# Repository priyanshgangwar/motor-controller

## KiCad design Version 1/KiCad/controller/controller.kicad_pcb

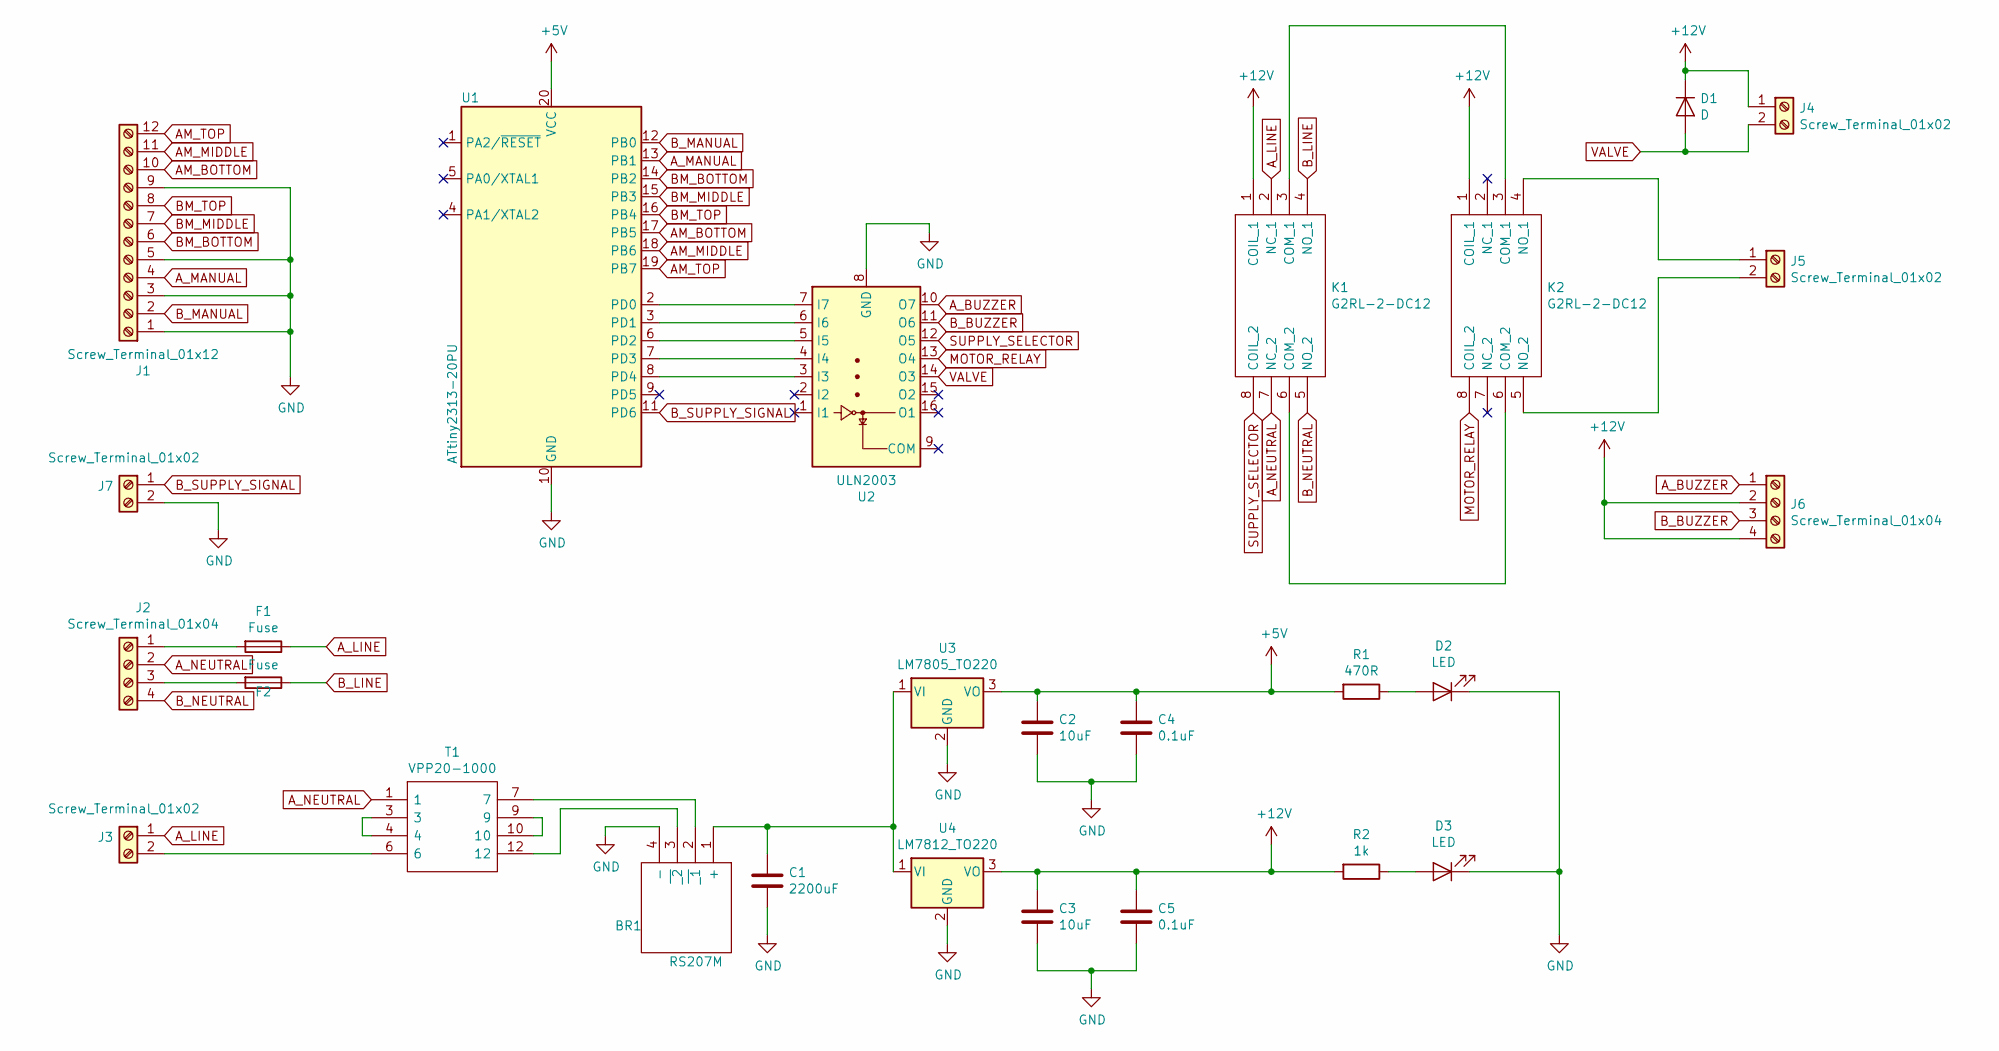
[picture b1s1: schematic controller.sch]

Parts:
BR1: RS207M; Mouser Part Number 583-RS207M
C1: 2200uF; CP_Radial_D16.0mm_P7.50mm
C2, C3: 10uF; CP_Radial_D5.0mm_P2.00mm
C4, C5: 0.1uF; CP_Radial_D5.0mm_P2.00mm
D1: D; D_DO-41_SOD81_P12.70mm_Horizontal
D2, D3: LED; LED_D5.0mm
F1, F2: Fuse; 646-SERIESHOLDER
J1: Screw_Terminal_01x12; TerminalBlock_Phoenix_MKDS-1,5-12_1x12_P5.00mm_Horizontal
J2, J6: Screw_Terminal_01x04; TerminalBlock_Phoenix_MKDS-1,5-4_1x04_P5.00mm_Horizontal
J3, J4, J5, J7: Screw_Terminal_01x02; TerminalBlock_Phoenix_MKDS-1,5-2_1x02_P5.00mm_Horizontal
K1, K2: G2RL-2-DC12; G2RL-24; Mouser Part Number 653-G2RL-2-DC12
R1: 470R; R_Axial_DIN0309_L9.0mm_D3.2mm_P12.70mm_Horizontal
R2: 1k; R_Axial_DIN0309_L9.0mm_D3.2mm_P12.70mm_Horizontal
T1: VPP20-1000; VPP201000; Mouser Part Number 553-VPP20-1000
U1: ATtiny2313-20PU; DIP-20_W7.62mm_Socket
U2: ULN2003; DIP-16_W7.62mm_Socket
U3: LM7805_TO220; TO-220-3_Vertical
U4: LM7812_TO220; TO-220-3_Vertical

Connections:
+5V: C2.1, C4.1, R1.2, U1.20 (VCC), U3.3 (VO)
+12V: C3.1, C5.1, D1.1 (K), J4.1, J6.2, J6.4, K1.1 (COIL_1), K2.1 (COIL_1), R2.2, U4.3 (VO)
AM_BOTTOM: J1.10, U1.17 (PB5)
AM_MIDDLE: J1.11, U1.18 (PB6)
AM_TOP: J1.12, U1.19 (PB7)
A_BUZZER: J6.1, U2.10 (O7)
A_LINE: F1.1, J3.1, K1.2 (NC_1)
A_MANUAL: J1.4, U1.13 (PB1)
A_NEUTRAL: J2.2, K1.7 (NC_2), T1.1
BM_BOTTOM: J1.6, U1.14 (PB2)
BM_MIDDLE: J1.7, U1.15 (PB3)
BM_TOP: J1.8, U1.16 (PB4)
B_BUZZER: J6.3, U2.11 (O6)
B_LINE: F2.1, K1.4 (NO_1)
B_MANUAL: J1.2, U1.12 (PB0)
B_NEUTRAL: J2.4, K1.5 (NO_2)
B_SUPPLY_SIGNAL: J7.1, U1.11 (PD6)
GND: BR1.4 (-), C1.2, C2.2, C3.2, C4.2, C5.2, D2.1 (K), D3.1 (K), J1.1, J1.3, J1.5, J1.9, J7.2, U1.10 (GND), U2.8 (GND), U3.2 (GND), U4.2 (GND)
MOTOR_RELAY: K2.8 (COIL_2), U2.13 (O4)
unnamed: BR1.1 (+), C1.1, U3.1 (VI), U4.1 (VI)
unnamed: BR1.2 (~_1), T1.7
unnamed: BR1.3 (~_2), T1.12
unnamed: D2.2 (A), R1.1
unnamed: D3.2 (A), R2.1
unnamed: F1.2, J2.1
unnamed: F2.2, J2.3
unnamed: J3.2, T1.6
unnamed: J5.1, K2.4 (NO_1)
unnamed: J5.2, K2.5 (NO_2)
unnamed: K1.3 (COM_1), K2.3 (COM_1)
unnamed: K1.6 (COM_2), K2.6 (COM_2)
unnamed: T1.3, T1.4
unnamed: T1.9, T1.10
unnamed: U1.2 (PD0), U2.7 (I7)
unnamed: U1.3 (PD1), U2.6 (I6)
unnamed: U1.6 (PD2), U2.5 (I5)
unnamed: U1.7 (PD3), U2.4 (I4)
unnamed: U1.8 (PD4), U2.3 (I3)
SUPPLY_SELECTOR: K1.8 (COIL_2), U2.12 (O5)
VALVE: D1.2 (A), J4.2, U2.14 (O3)

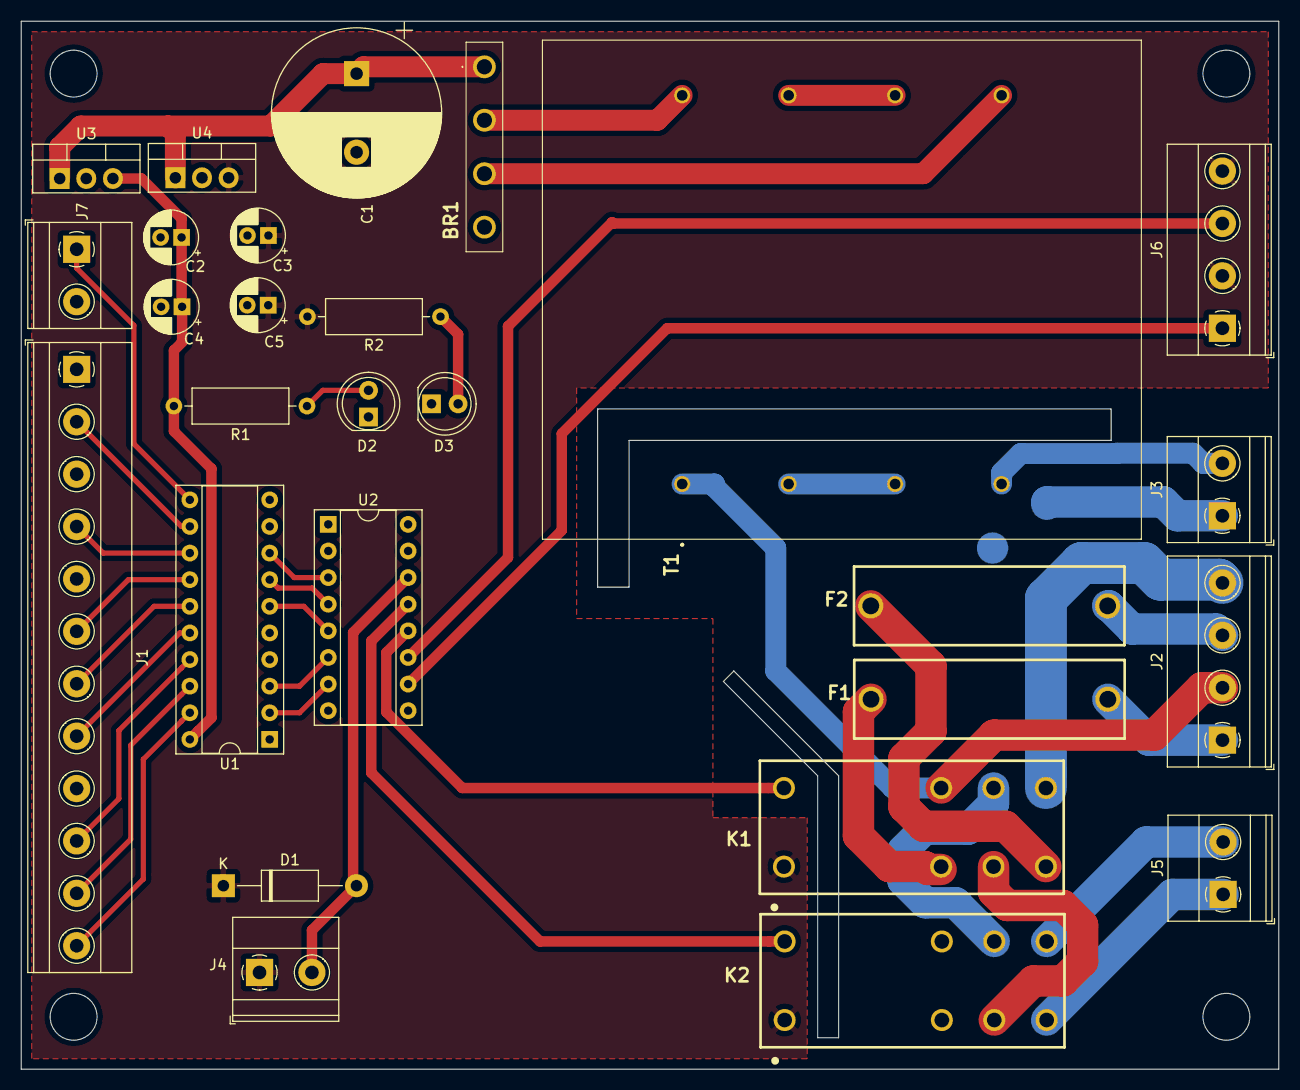
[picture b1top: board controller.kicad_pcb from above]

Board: 2 copper layers, 120.0 x 100.0 mm, 27 parts (0 on the bottom side), 40 nets.

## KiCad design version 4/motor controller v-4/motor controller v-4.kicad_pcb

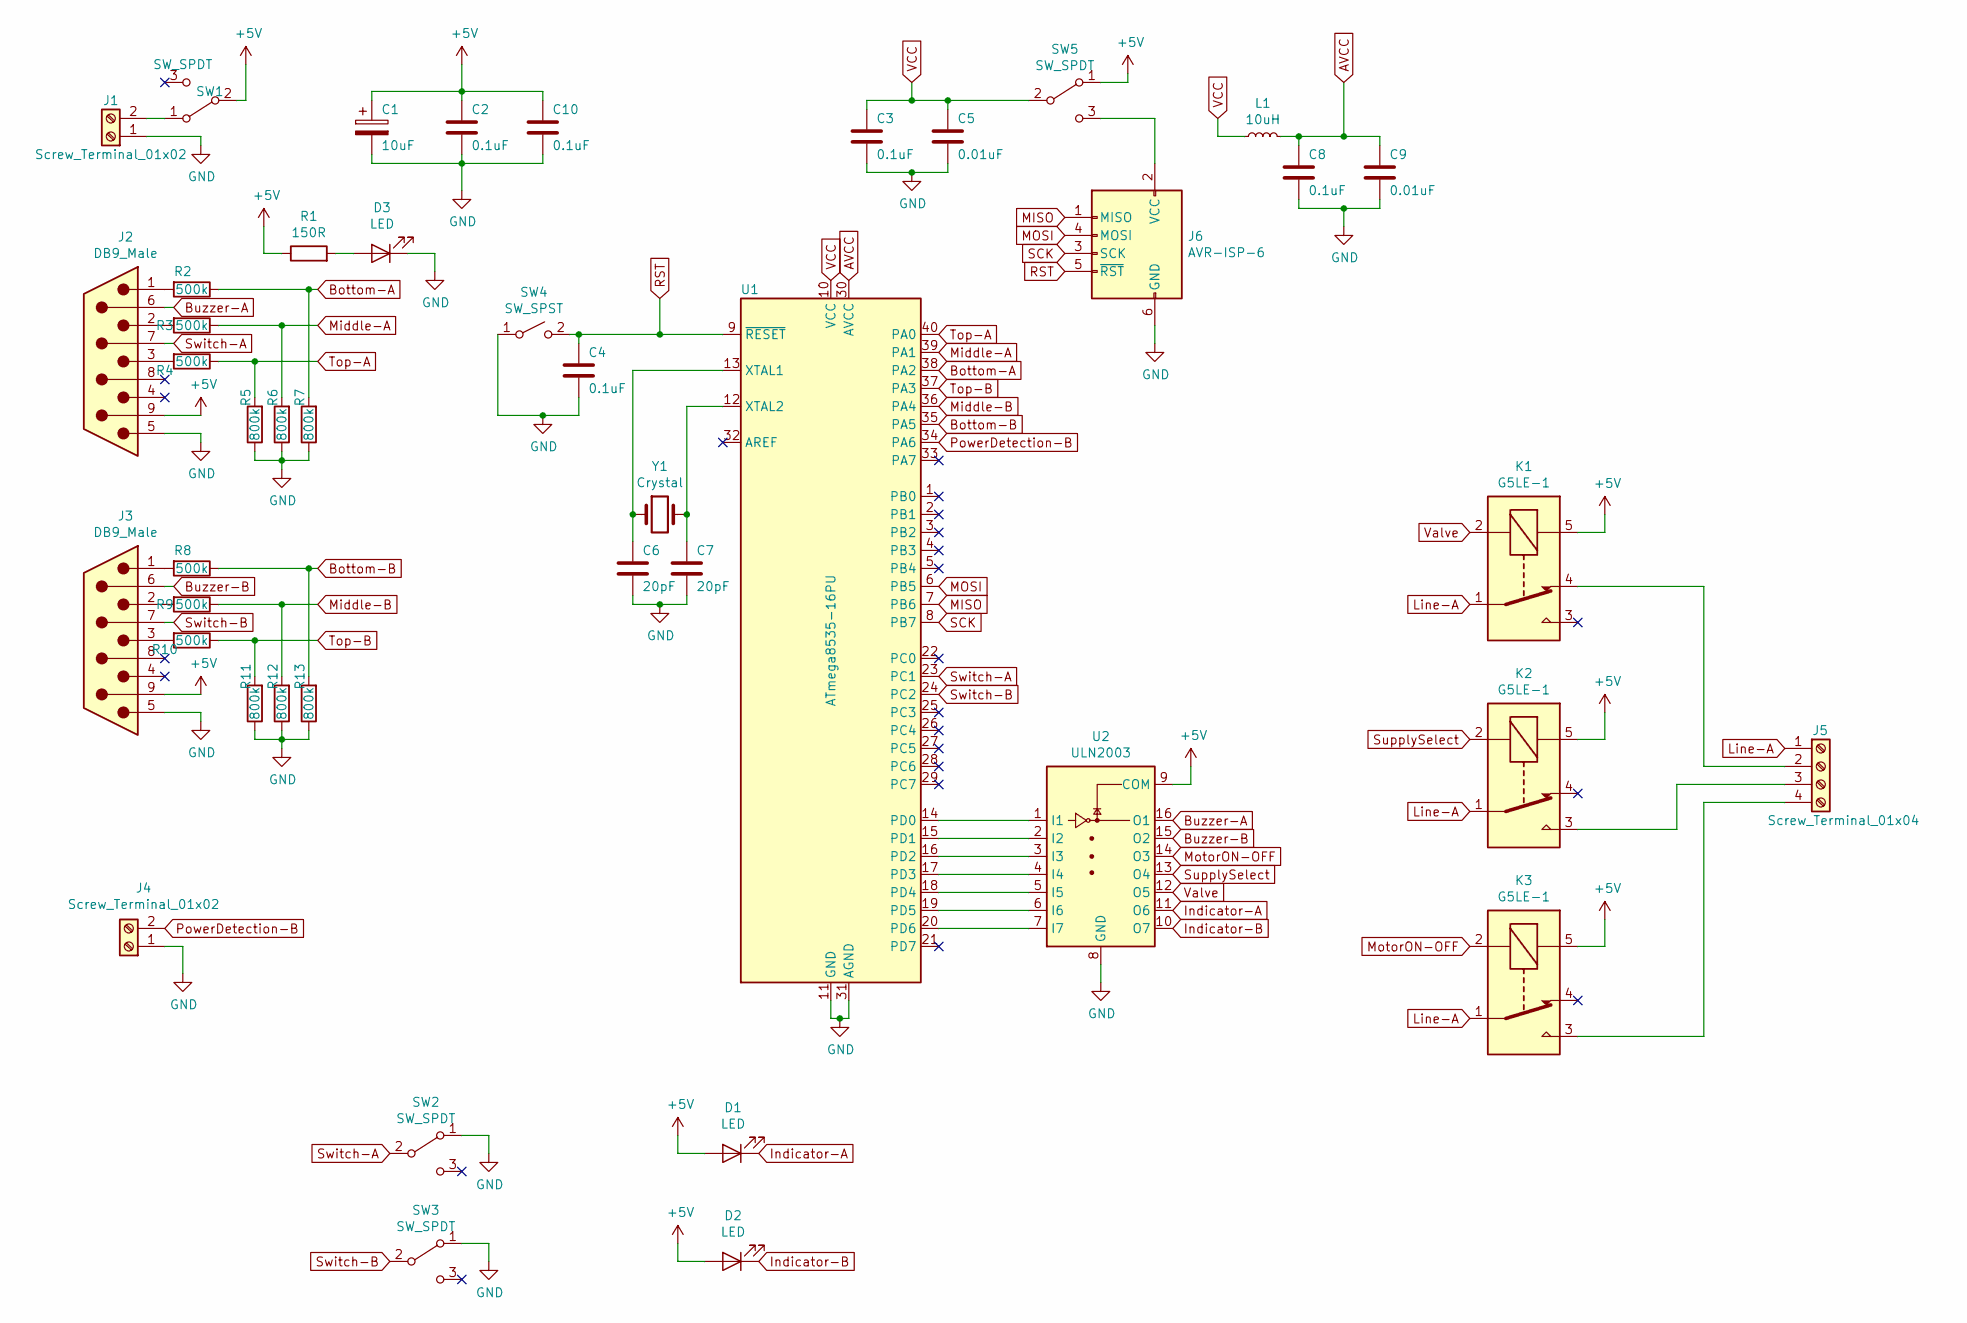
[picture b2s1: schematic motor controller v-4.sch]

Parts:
C1: 10uF; CP_Radial_D5.0mm_P2.00mm
C2, C3, C4, C8, C10: 0.1uF; C_Disc_D5.0mm_W2.5mm_P2.50mm
C5, C9: 0.01uF; C_Disc_D5.0mm_W2.5mm_P2.50mm
C6, C7: 20pF; C_Disc_D5.0mm_W2.5mm_P2.50mm
D1, D2, D3: LED; LED_D5.0mm
J1, J4: Screw_Terminal_01x02; TerminalBlock_bornier-2_P5.08mm
J2, J3: DB9_Male; DSUB-9_Male_Horizontal_P2.77x2.84mm_EdgePinOffset4.94mm_Hou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
J5: Screw_Terminal_01x04; TerminalBlock_bornier-4_P5.08mm
J6: AVR-ISP-6; PinSocket_2x03_P2.54mm_Vertical
K1, K2, K3: G5LE-1; Relay_SPDT_Omron-G5LE-1
L1: 10uH; L_Radial_D6.0mm_P4.00mm
R1: 150R; R_Axial_DIN0411_L9.9mm_D3.6mm_P7.62mm_Vertical
R2, R3, R4, R8, R9, R10: 500k; R_Axial_DIN0207_L6.3mm_D2.5mm_P10.16mm_Horizontal
R5, R6, R7, R11, R12, R13: 800k; R_Axial_DIN0207_L6.3mm_D2.5mm_P10.16mm_Horizontal
SW1, SW2, SW3, SW5: SW_SPDT; SPDT Switch
SW4: SW_SPST; SW_PUSH_6mm_H5mm
U1: ATmega8535-16PU; DIP-40_W15.24mm
U2: ULN2003; DIP-16_W7.62mm_Socket_LongPads
Y1: Crystal; Crystal_HC50_Vertical

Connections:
+5V: C1.1, C2.1, C10.1, D1.2 (A), D2.2 (A), J2.9, J3.9, K1.5, K2.5, K3.5, R1.1, SW1.2 (B), SW5.1 (A), U2.9 (COM)
AVCC: C8.1, C9.1, L1.2, U1.30 (AVCC)
Bottom-A: R2.1, R7.2, U1.38 (PA2)
Bottom-B: R8.1, R13.2, U1.35 (PA5)
Buzzer-A: J2.6, U2.16 (O1)
Buzzer-B: J3.6, U2.15 (O2)
GND: C1.2, C2.2, C3.2, C4.2, C5.2, C6.2, C7.2, C8.2, C9.2, C10.2, D3.1 (K), J1.1, J2.5, J3.5, J4.1, J6.6 (GND), R5.1, R6.1, R7.1, R11.1, R12.1, R13.1, SW2.1 (A), SW3.1 (A), SW4.1 (A), U1.11 (GND), U1.31 (AGND), U2.8 (GND)
Indicator-A: D1.1 (K), U2.11 (O6)
Indicator-B: D2.1 (K), U2.10 (O7)
Line-A: J5.1, K1.1, K2.1, K3.1
MISO: J6.1 (MISO), U1.7 (PB6)
MOSI: J6.4 (MOSI), U1.6 (PB5)
Middle-A: R3.1, R6.2, U1.39 (PA1)
Middle-B: R9.1, R12.2, U1.36 (PA4)
MotorON-OFF: K3.2, U2.14 (O3)
unnamed: C6.1, U1.13 (XTAL1), Y1.1
unnamed: C7.1, U1.12 (XTAL2), Y1.2
unnamed: D3.2 (A), R1.2
unnamed: J1.2, SW1.1 (A)
unnamed: J2.1, R2.2
unnamed: J2.2, R3.2
unnamed: J2.3, R4.2
unnamed: J3.1, R8.2
unnamed: J3.2, R9.2
unnamed: J3.3, R10.2
unnamed: J5.2, K1.4
unnamed: J5.3, K2.3
unnamed: J5.4, K3.3
unnamed: J6.2 (VCC), SW5.3 (C)
unnamed: U1.14 (PD0), U2.1 (I1)
unnamed: U1.15 (PD1), U2.2 (I2)
unnamed: U1.16 (PD2), U2.3 (I3)
unnamed: U1.17 (PD3), U2.4 (I4)
unnamed: U1.18 (PD4), U2.5 (I5)
unnamed: U1.19 (PD5), U2.6 (I6)
unnamed: U1.20 (PD6), U2.7 (I7)
PowerDetection-B: J4.2, U1.34 (PA6)
RST: C4.1, J6.5 (~RST), SW4.2 (B), U1.9 (~RESET)
SCK: J6.3 (SCK), U1.8 (PB7)
SupplySelect: K2.2, U2.13 (O4)
Switch-A: J2.7, SW2.2 (B), U1.23 (PC1)
Switch-B: J3.7, SW3.2 (B), U1.24 (PC2)
Top-A: R4.1, R5.2, U1.40 (PA0)
Top-B: R10.1, R11.2, U1.37 (PA3)
VCC: C3.1, C5.1, L1.1, SW5.2 (B), U1.10 (VCC)
Valve: K1.2, U2.12 (O5)

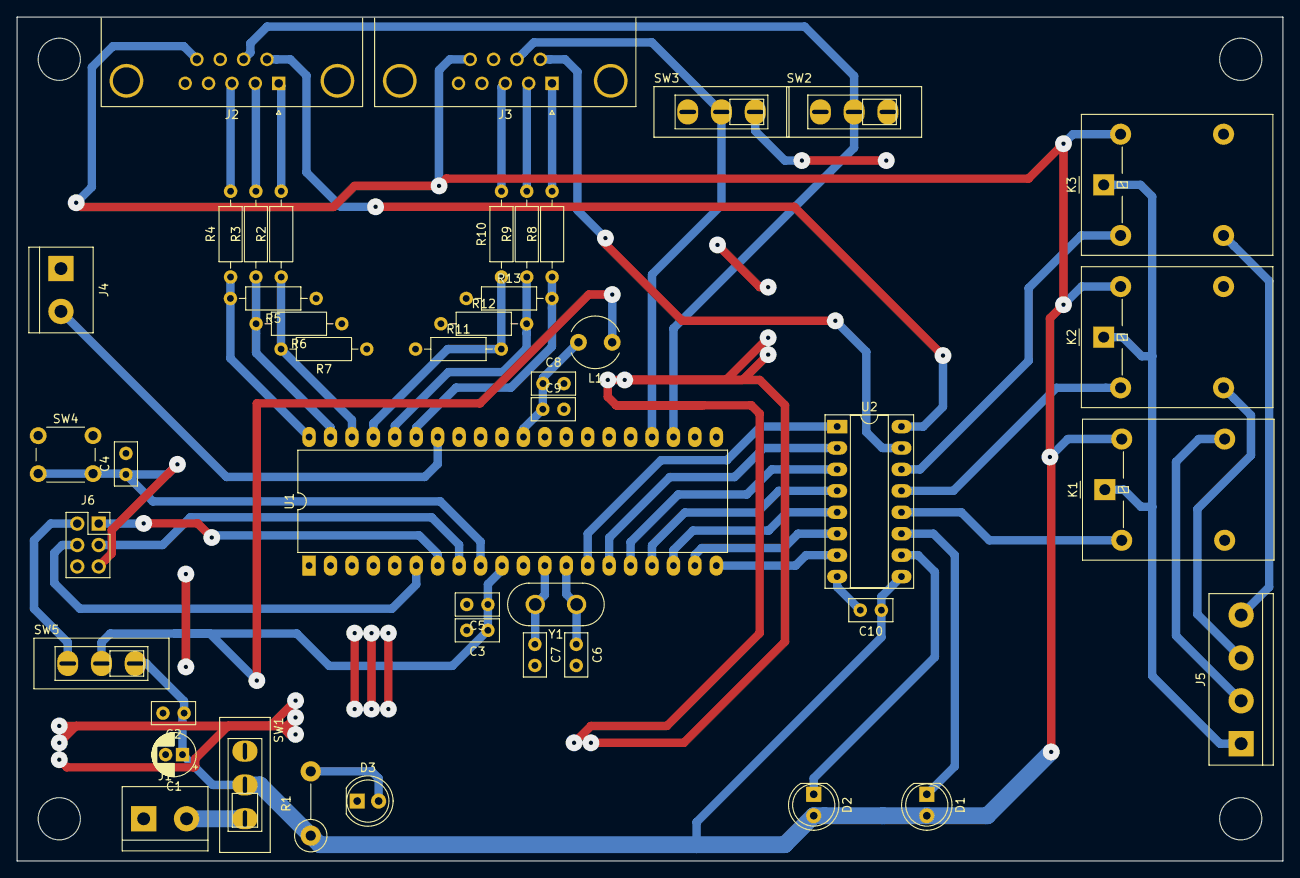
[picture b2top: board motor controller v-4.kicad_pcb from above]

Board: 2 copper layers, 150.0 x 100.0 mm, 44 parts (0 on the bottom side), 46 nets.

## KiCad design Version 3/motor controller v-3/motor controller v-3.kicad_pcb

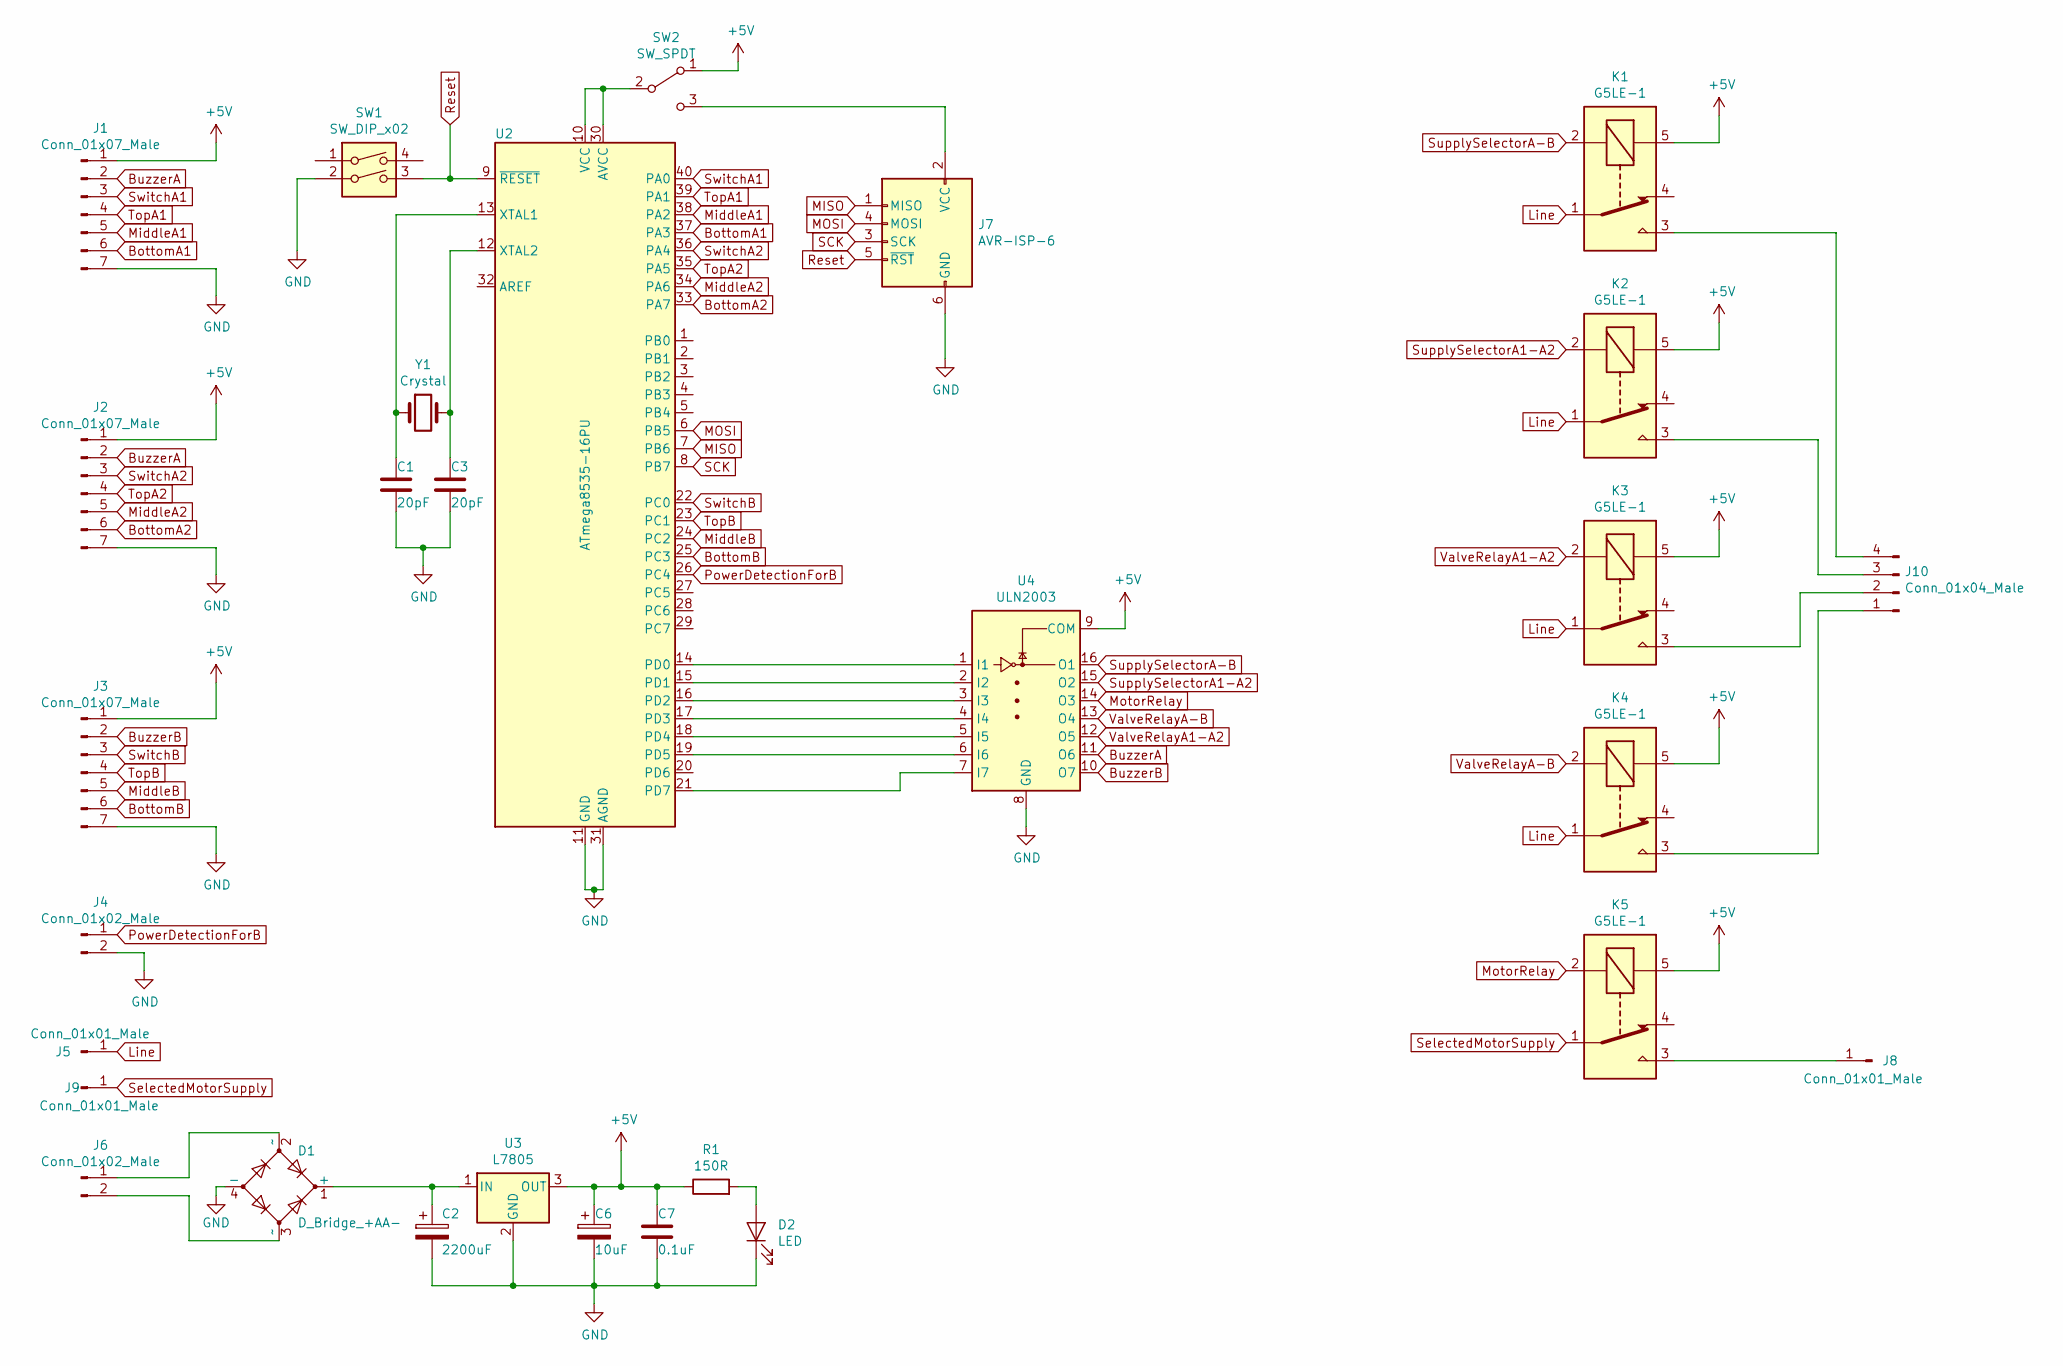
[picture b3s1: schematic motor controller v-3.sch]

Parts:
C1, C3: 20pF; C_Disc_D5.0mm_W2.5mm_P2.50mm
C2: 2200uF; CP_Radial_D13.0mm_P7.50mm
C6: 10uF; CP_Radial_D5.0mm_P2.50mm
C7: 0.1uF; C_Disc_D5.0mm_W2.5mm_P2.50mm
D1: D_Bridge_+AA-; Diode_Bridge_19.0x3.5x10.0mm_P5.0mm
D2: LED; LED_D5.0mm
J1, J2, J3: Conn_01x07_Male; PinHeader_1x07_P2.54mm_Vertical
J4, J6: Conn_01x02_Male; PinHeader_1x02_P2.54mm_Vertical
J5, J8, J9: Conn_01x01_Male; PinHeader_1x01_P2.54mm_Vertical
J7: AVR-ISP-6; PinHeader_2x03_P2.54mm_Vertical
J10: Conn_01x04_Male; PinHeader_1x04_P2.54mm_Vertical
K1, K2, K3, K4, K5: G5LE-1; Relay_SPDT_Omron-G5LE-1
R1: 150R; R_Axial_DIN0309_L9.0mm_D3.2mm_P15.24mm_Horizontal
SW1: SW_DIP_x02; Push_E-Switch_KS01Q01
SW2: SW_SPDT; TO-220-3_Vertical
U2: ATmega8535-16PU; DIP-40_W15.24mm
U3: L7805; TO-220-3_Vertical
U4: ULN2003; DIP-16_W7.62mm
Y1: Crystal; Crystal_HC18-U_Vertical

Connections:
+5V: C6.1, C7.1, J1.1, J2.1, J3.1, K1.5, K2.5, K3.5, K4.5, K5.5, R1.1, SW2.1 (A), U3.3 (OUT), U4.9 (COM)
BottomA1: J1.6, U2.37 (PA3)
BottomA2: J2.6, U2.33 (PA7)
BottomB: J3.6, U2.25 (PC3)
BuzzerA: J1.2, J2.2, U4.11 (O6)
BuzzerB: J3.2, U4.10 (O7)
GND: C1.2, C2.2, C3.2, C6.2, C7.2, D1.4 (-), D2.1 (K), J1.7, J2.7, J3.7, J4.2, J7.6 (GND), SW1.2, U2.11 (GND), U2.31 (AGND), U3.2 (GND), U4.8 (GND)
Line: J5.1, K1.1, K2.1, K3.1, K4.1
MISO: J7.1 (MISO), U2.7 (PB6)
MOSI: J7.4 (MOSI), U2.6 (PB5)
MiddleA1: J1.5, U2.38 (PA2)
MiddleA2: J2.5, U2.34 (PA6)
MiddleB: J3.5, U2.24 (PC2)
MotorRelay: K5.2, U4.14 (O3)
unnamed: C1.1, U2.13 (XTAL1), Y1.1
unnamed: C2.1, D1.1 (+), U3.1 (IN)
unnamed: C3.1, U2.12 (XTAL2), Y1.2
unnamed: D1.2 (~~), J6.1
unnamed: D1.3 (~~), J6.2
unnamed: D2.2 (A), R1.2
unnamed: J7.2 (VCC), SW2.3 (C)
unnamed: J8.1, K5.3
unnamed: J10.1, K4.3
unnamed: J10.2, K3.3
unnamed: J10.3, K2.3
unnamed: J10.4, K1.3
unnamed: SW2.2 (B), U2.10 (VCC), U2.30 (AVCC)
unnamed: U2.14 (PD0), U4.1 (I1)
unnamed: U2.15 (PD1), U4.2 (I2)
unnamed: U2.16 (PD2), U4.3 (I3)
unnamed: U2.17 (PD3), U4.4 (I4)
unnamed: U2.18 (PD4), U4.5 (I5)
unnamed: U2.19 (PD5), U4.6 (I6)
unnamed: U2.21 (PD7), U4.7 (I7)
PowerDetectionForB: J4.1, U2.26 (PC4)
Reset: J7.5 (~RST), SW1.3, U2.9 (~RESET)
SCK: J7.3 (SCK), U2.8 (PB7)
SelectedMotorSupply: J9.1, K5.1
SupplySelectorA1-A2: K2.2, U4.15 (O2)
SupplySelectorA-B: K1.2, U4.16 (O1)
SwitchA1: J1.3, U2.40 (PA0)
SwitchA2: J2.3, U2.36 (PA4)
SwitchB: J3.3, U2.22 (PC0)
TopA1: J1.4, U2.39 (PA1)
TopA2: J2.4, U2.35 (PA5)
TopB: J3.4, U2.23 (PC1)
ValveRelayA1-A2: K3.2, U4.12 (O5)
ValveRelayA-B: K4.2, U4.13 (O4)

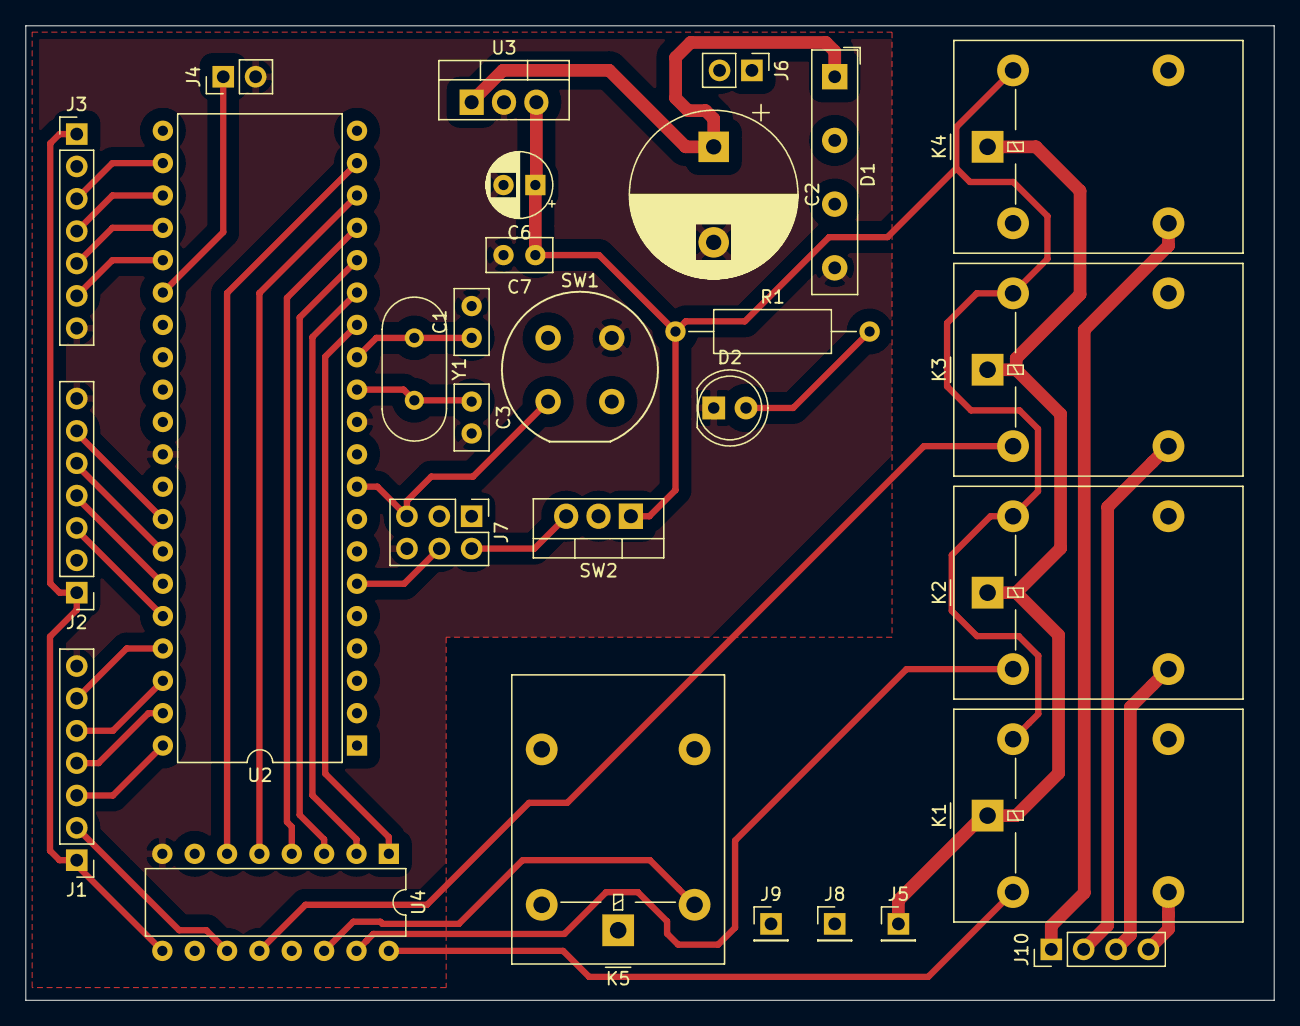
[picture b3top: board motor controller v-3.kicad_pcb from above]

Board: 2 copper layers, 98.0 x 76.5 mm, 29 parts (0 on the bottom side), 48 nets.

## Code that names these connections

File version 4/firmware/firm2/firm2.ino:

#include <SoftwareSerial.h>

//Constants
const int valve_wait_time = 8000;
const byte short_beep = 10;
const byte long_beep = 20;

SoftwareSerial mySerial(2, 3); // RX, TX

//Variables

//All inputs
//Top = red
//middle = yellow
//bottom = white
//common = gray
const byte a_tank_top = 24;
const byte a_tank_middle = 25;
const byte a_tank_bottom = 26;
const byte a_manual_start = 17;
const byte b_tank_top = 27;
const byte b_tank_middle = 28;
const byte b_tank_bottom = 29;
const byte b_manual_start = 18;
const byte b_supply_detect = 30;

//All outputs
const byte a_buzzer = 8;
const byte b_buzzer = 9;
const byte supply_selector_relay = 11;
const byte motor_relay = 10;
const byte valve_relay = 12;
const byte a_indicator = 13;
const byte b_indicator = 14;

void setup() {
	// put your setup code here, to run once:
	pinMode(a_manual_start, INPUT_PULLUP);
	pinMode(b_manual_start, INPUT_PULLUP);
	pinMode(b_supply_detect, INPUT_PULLUP);

	pinMode(a_buzzer, OUTPUT);
	pinMode(b_buzzer, OUTPUT);
	pinMode(supply_selector_relay, OUTPUT);
	pinMode(motor_relay, OUTPUT);
	pinMode(valve_relay, OUTPUT);
	pinMode(a_indicator, OUTPUT);
	pinMode(b_indicator, OUTPUT);

 // Open serial communications and wait for port to open:
  Serial.begin(57600);
  while (!Serial); // wait for serial port to connect. Needed for native USB port only 

  Serial.println("Goodnight moon!");

  // Set the data rate for the SoftwareSerial port
  mySerial.begin(4800);
  mySerial.println("Hello, world?");
}

void loop() {
	// put your main code here, to run repeatedly:
	checkForA();
}


//controls the auto and manual motor on/off functions for home A
void checkForA() {
  //if the water lavel is below bottom sensor
  //turn the motor on
  if(checkTank(a_tank_top, a_tank_middle, a_tank_bottom) == 3){
    mySerial.println("water lavel is below bottom sensor. Motor ON.");
    digitalWrite(motor_relay, HIGH);
    digitalWrite(a_indicator, HIGH);
    digitalWrite(a_buzzer, HIGH);
    int counter = 0;
    bool buzzer_state = true;
    while(true){
      if(counter >= 1 && buzzer_state){
        digitalWrite(a_buzzer, LOW);
        buzzer_state = false;
        counter = 0;
      }
      else if(counter >= 20 && !buzzer_state){
        digitalWrite(a_buzzer, HIGH);
        buzzer_state = true;
        counter = 0;
      }
      counter++;
      //If the water level gets above middle sensor
      //turn the motor off
      if(checkTank(a_tank_top, a_tank_middle, a_tank_bottom) == 1){
        mySerial.println("water lavel is above middle sensor. Motor OFF.");
        digitalWrite(motor_relay, LOW);
        digitalWrite(a_indicator, LOW);
        digitalWrite(a_buzzer, LOW);
        break;
      }
      
      //keep checking for the manual on switch of Home A
      manualSwitchControlA();
    }
  }
  //keep checking for the manual on switch of Home A
  manualSwitchControlA();
}

void manualSwitchControlA(){
  if(digitalRead(a_manual_start) == LOW){
    mySerial.println("Manual swith is ON");
    digitalWrite(motor_relay, HIGH);
    digitalWrite(a_indicator, HIGH);
    digitalWrite(a_buzzer, HIGH);
    int counter = 0;
    bool buzzer_state = true;
    while(checkTank(a_tank_top, a_tank_middle, a_tank_bottom) >= 1 && digitalRead(a_manual_start) == LOW){
      if(counter >= 2 && buzzer_state){
        digitalWrite(a_buzzer, LOW);
        buzzer_state = false;
        counter = 0;
      }
      else if(counter >= 5 && !buzzer_state){
        digitalWrite(a_buzzer, HIGH);
        buzzer_state = true;
        counter = 0;
      }
      counter++;
    }
    while(checkTank(a_tank_top, a_tank_middle, a_tank_bottom) == 0 && digitalRead(a_manual_start) == LOW){
      digitalWrite(a_buzzer, !digitalRead(a_buzzer));
    }
    digitalWrite(motor_relay, LOW);
    digitalWrite(a_indicator, LOW);
    digitalWrite(a_buzzer, LOW);
  }
}

//return 0 if top is in water else
//return 1 if middle is in water else
//return 2 if botom is in water else
//return 3 if no sensor is in water
int checkTank(byte top, byte middle, byte bottom){
  float value = checkVoltage(top);
  mySerial.print(value);
  mySerial.print("    ");
  value = checkVoltage(middle);
  mySerial.println(value);
  mySerial.print("    ");
  value = checkVoltage(bottom);
  mySerial.println(value);
  mySerial.println();

  if(checkVoltage(top) > 1) {
    return 0;
  }
  else if(checkVoltage(middle) > 1){
    return 1;
  }
  else if(checkVoltage(bottom) > 1){
    return 2;
  }
  else return 3;
}

float checkVoltage(byte sensor){
  long total = 0;
  for(int i=0; i<1000; i++){
    // read the input on analog pin 0:
    int sensorValue = analogRead(sensor);
    // Convert the analog reading (which goes from 0 - 1023) to a voltage (0 - 5V):
    total += sensorValue;
    //Serial.println(total);
    //delay(500);
  }

  total /= 1000;
  float voltage = total * (5.0 / 1023.0);
    // print out the value you read:
  return voltage;
}
